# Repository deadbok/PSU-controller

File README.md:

A bench PSU controller using PIC16F887

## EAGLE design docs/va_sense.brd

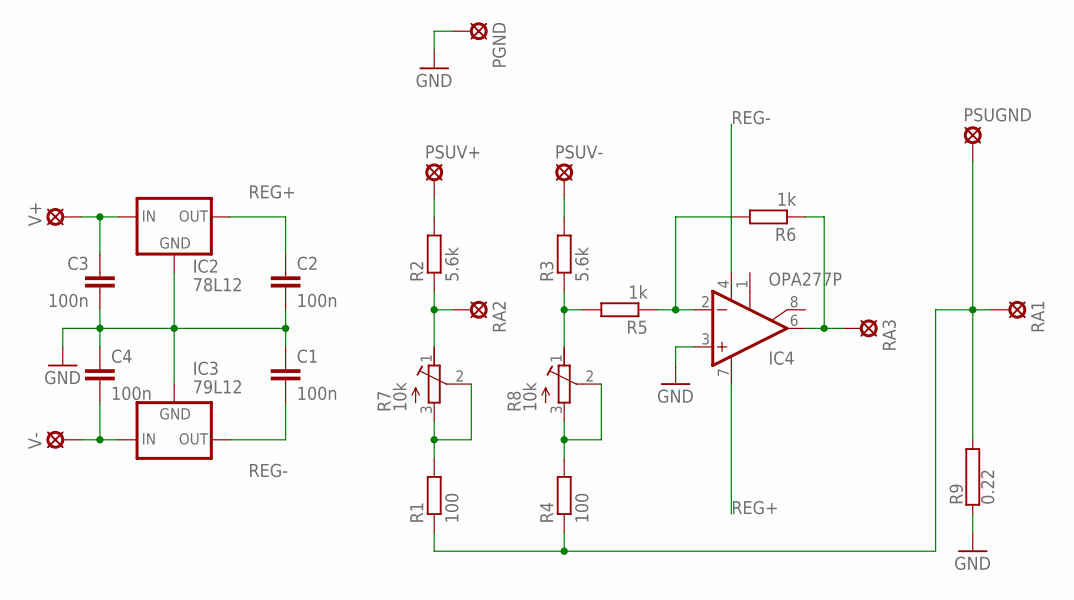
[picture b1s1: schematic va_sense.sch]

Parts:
C1, C2, C3, C4: 100n; C0805K
IC2: 78L12; 78LXX
IC3: 79L12; 79LXX
IC4: OPA277P; DIL08
PGND: SE13
PSUGND: SE13
PSUV+: SE13
PSUV-: SE13
R1, R4: 100; 0207/10
R2, R3: 5.6k; 0207/10
R5, R6: 1k; 0207/10
R7, R8: 10k; RTRIM3006P
R9: 0.22; KH208-8
RA1, RA2, RA3: SE13
V+: SE13
V-: SE13

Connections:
GND: C1.1, C2.2, C3.2, C4.1, IC2.GND, IC3.GND, IC4.3 (+IN), PGND.MP, R9.1
unnamed: R1.2, R7.2 (S), R7.3 (E)
unnamed: R2.1, R7.1 (A), RA2.MP
unnamed: R3.1, R5.2, R8.1 (A)
unnamed: R4.2, R8.2 (S), R8.3 (E)
unnamed: IC4.2 (-IN), R5.1, R6.2
unnamed: IC4.6 (OUT), R6.1, RA3.MP
unnamed: PSUV+.MP, R2.2
unnamed: PSUV-.MP, R3.2
unnamed: PSUGND.MP, R1.1, R4.1, R9.2, RA1.MP
unnamed: C3.1, IC2.IN, V+.MP
unnamed: C4.2, IC3.IN, V-.MP
REG+: C2.1, IC2.OUT, IC4.7 (V+)
REG-: C1.2, IC3.OUT, IC4.4 (V-)

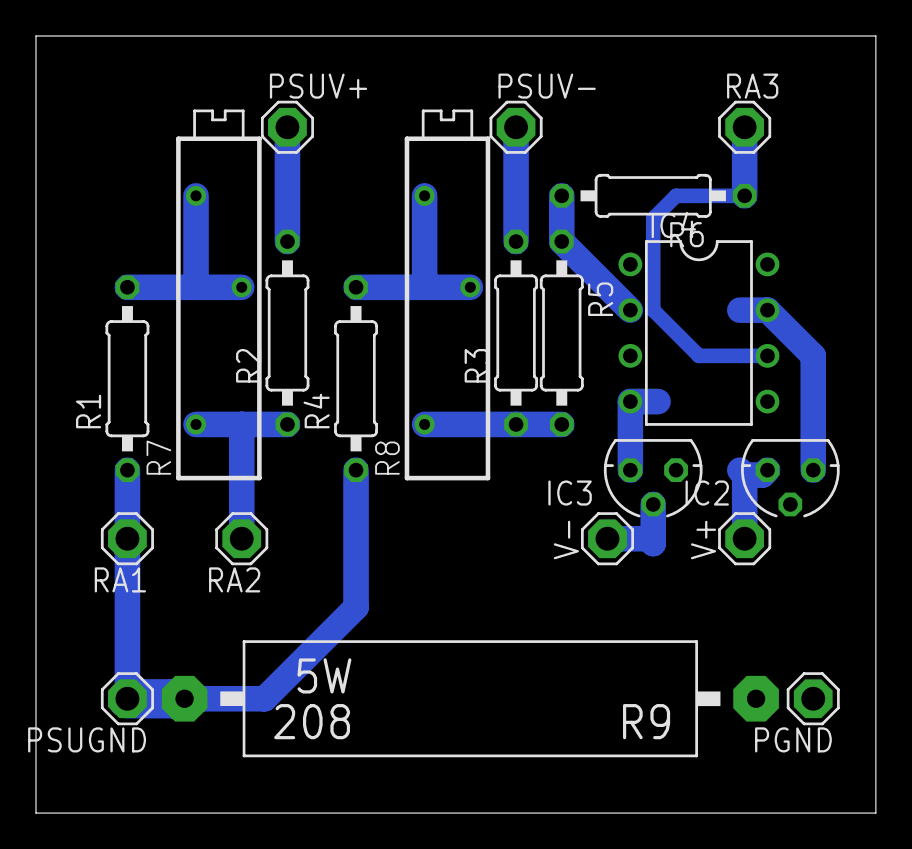
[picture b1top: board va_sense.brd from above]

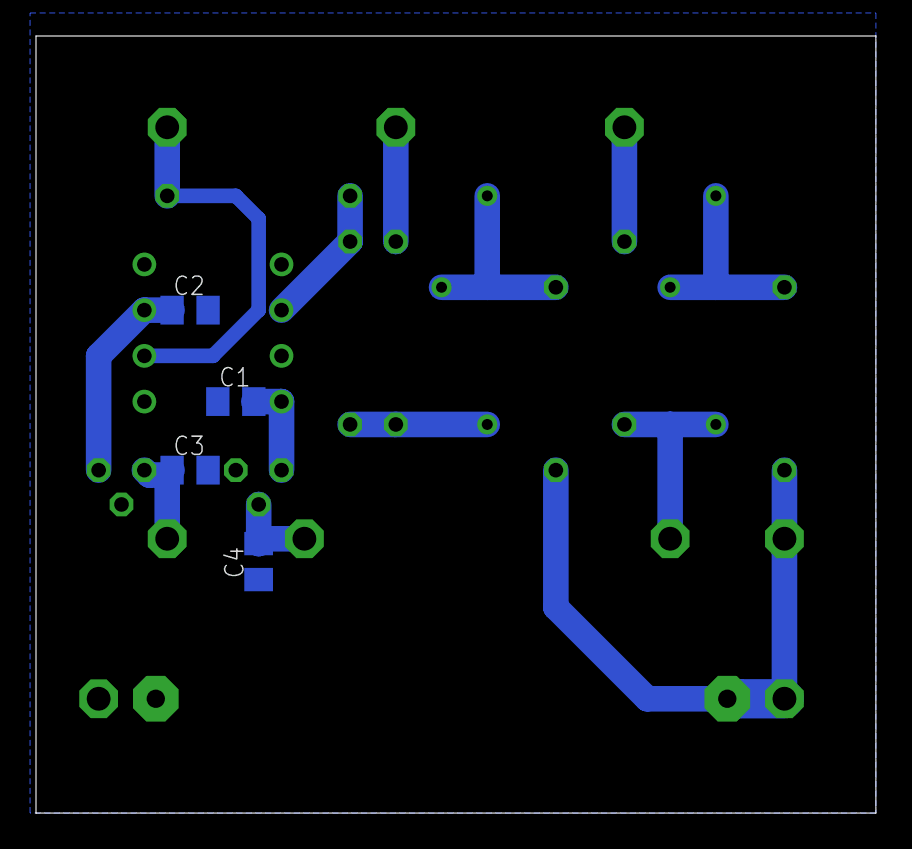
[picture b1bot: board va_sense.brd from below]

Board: 2 copper layers, 46.7 x 43.2 mm, 25 parts (4 on the bottom side), 14 nets.

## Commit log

2013-03-03 README for Github
